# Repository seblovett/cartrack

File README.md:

cartrack
========

A car tracking system using GPS and GSM

Current Capabilities
====================

The GSM has been prototyped and proven to work. 

PCB is V1.0 and not been made nor tested.

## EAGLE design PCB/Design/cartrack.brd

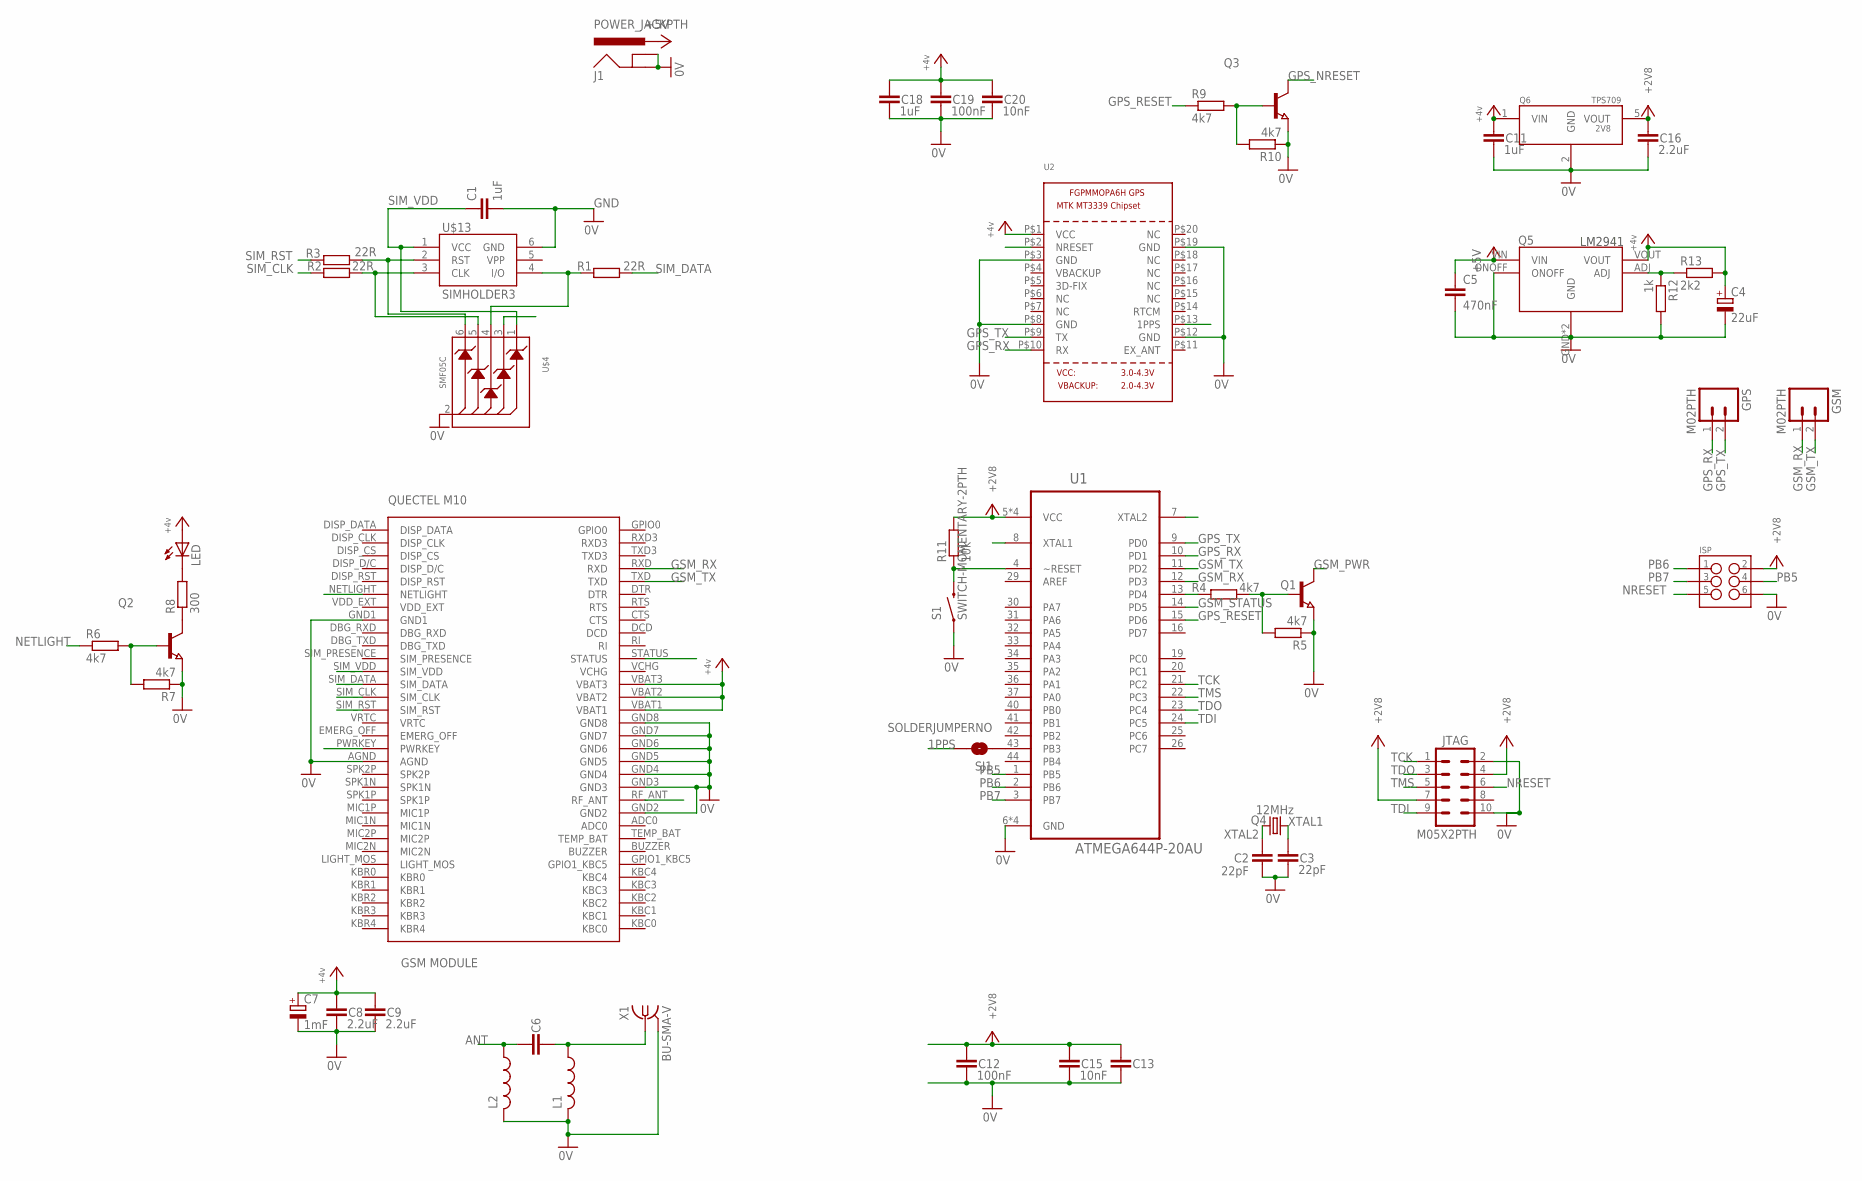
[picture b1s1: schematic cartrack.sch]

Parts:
C1: 1uF; C0603
C2, C3: 22pF; 0603-CAP
C4: 22uF; E3,5-8
C5: 470nF; C025-024X044
C6, C13: CAP0603-CAP; 0603-CAP
C7: 1mF; E3,5-8
C8, C9, C16: 2.2uF; 1206
C11: 1uF; 1206
C12, C19: 100nF; 1206
C15, C20: 10nF; 0603-CAP
C18: 1uF; CAP-PTH-SMALL
GPS: M02PTH; 1X02
GSM: M02PTH; 1X02
ISP: M03X2NO_SILK; 2X3-NS
J1: POWER_JACKPTH; POWER_JACK_PTH
JTAG: M05X2PTH; AVR_ICSP
L1, L2: L-USL2012C; L2012C
LED: LEDSML0603; SML0603
Q1, Q2, Q3: NPN-TRANSISTOR_SOT23W; SOT23W
Q4: 12MHz; SM49
Q5: LM2941
Q6: TPS70928; SOT23-5
R1, R2, R3: 22R; R0603
R4, R5, R6, R7, R9, R10: 4k7; R0603
R8: 300; R0603
R11: 10k; R0603
R12: 1k; R0603
R13: 2k2; R0603
S1: SWITCH-MOMENTARY-2PTH; TACTILE-PTH
SJ1: SOLDERJUMPERNO; SJ_2S-NO
U1: ATMEGA644P-20AU; QFP80P1200X1200X120-44N
U2: GPS_FGPMMOPA6H; FGPMMOPA6H
U$1: QUECTELM10
U$4: SMF05C; SC-88
U$13: SIMHOLDER3
X1: BU-SMA-V

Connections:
1PPS: SJ1.2, U2.P$13 (1PPS)
+2V8: C12.1, C13.1, C15.1, C16.1, ISP.2, JTAG.4, JTAG.7, Q6.5 (VOUT), R11.2, U1.5 (VCC), U1.17 (VCC), U1.27 (VCC), U1.38 (VCC)
+4V: C4.+, C7.+, C8.1, C9.1, C11.1, C18.1, C19.1, C20.1, LED.A, Q5.VOUT, Q6.1 (VIN), R13.2, U2.P$1 (VCC), U$1.VBAT1, U$1.VBAT2, U$1.VBAT3
+5V: C5.1, J1.PWR, Q5.VIN
ANT: C6.1, L2.1, U$1.RF_ANT
ANT_1: C6.2, L1.1, X1.1
GND: C1.2, C2.2, C3.2, C4.-, C5.2, C7.-, C8.2, C9.2, C11.2, C12.2, C13.2, C15.2, C16.2, C18.2, C19.2, C20.2, ISP.6, J1.GND, J1.GNDBREAK, JTAG.2, JTAG.10, L1.2, L2.2, Q1.3 (E), Q2.3 (E), Q3.3 (E), Q5.GND, Q5.ONOFF, Q5.TAB (GND), Q6.2 (GND), R5.1, R7.1, R10.1, R12.2, S1.1, U2.P$3 (GND), U2.P$8 (GND), U2.P$12 (GND), U2.P$19 (GND), U$1.AGND, U$1.GND1, U$1.GND2, U$1.GND3, U$1.GND4, U$1.GND5, U$1.GND6, U$1.GND7, U$1.GND8, U$4.2 (ANODE), U$13.6 (GND), X1.2, X1.3 (2), X1.4 (2), X1.5 (2)
GPS_NRESET: Q3.2 (C), U2.P$2 (NRESET)
GPS_RESET: R9.1, U1.15 (PD6)
GPS_RX: GPS.1, U1.10 (PD1), U2.P$10 (RX)
GPS_TX: GPS.2, U1.9 (PD0), U2.P$9 (TX)
GSM_PWR: Q1.2 (C), U$1.PWRKEY, U$4.3 (CATODE2)
GSM_RX: GSM.1, U1.12 (PD3), U$1.RXD
GSM_STATUS: U1.14 (PD5), U$1.STATUS
GSM_TX: GSM.2, U1.11 (PD2), U$1.TXD
unnamed: Q1.1 (B), R4.2, R5.2
unnamed: R4.1, U1.13 (PD4)
unnamed: Q5.ADJ, R12.1, R13.1
unnamed: Q2.1 (B), R6.2, R7.2
unnamed: Q2.2 (C), R8.1
unnamed: LED.C, R8.2
unnamed: Q3.1 (B), R9.2, R10.2
unnamed: SJ1.1, U1.43 (PB3)
NETLIGHT: R6.1, U$1.NETLIGHT
NRESET: ISP.5, JTAG.6, R11.1, S1.3 (2), U1.4 (~RESET)
PB5: ISP.4, U1.1 (PB5)
PB6: ISP.1, U1.2 (PB6)
PB7: ISP.3, U1.3 (PB7)
SIM_CLK: R2.1, U$1.SIM_CLK
SIM_CLK_R: R2.2, U$4.5 (CATODE4), U$13.3 (CLK)
SIM_DATA: R1.2, U$1.SIM_DATA
SIM_DATA_R: R1.1, U$4.4 (CATODE3), U$13.4 (I/O)
SIM_RST: R3.1, U$1.SIM_RST
SIM_RST_R: R3.2, U$4.6 (CATODE5), U$13.2 (RST)
SIM_VDD: C1.1, U$1.SIM_VDD, U$4.1 (CATODE1), U$13.1 (VCC)
TCK: JTAG.1, U1.21 (PC2)
TDI: JTAG.9, U1.24 (PC5)
TDO: JTAG.3, U1.23 (PC4)
TMS: JTAG.5, U1.22 (PC3)
XTAL1: C3.1, Q4.2, U1.8 (XTAL1)
XTAL2: C2.1, Q4.1, U1.7 (XTAL2)

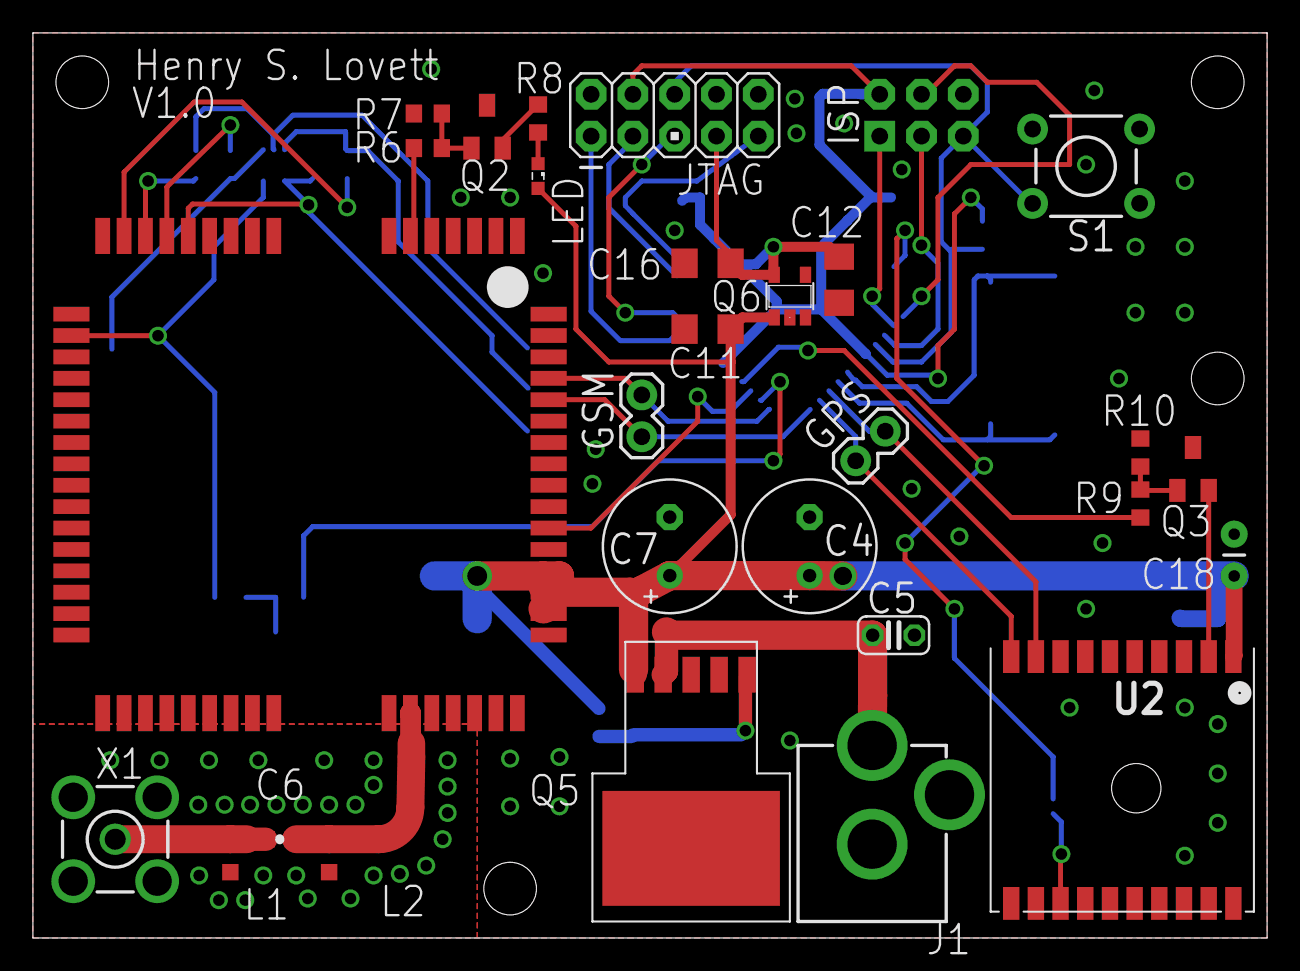
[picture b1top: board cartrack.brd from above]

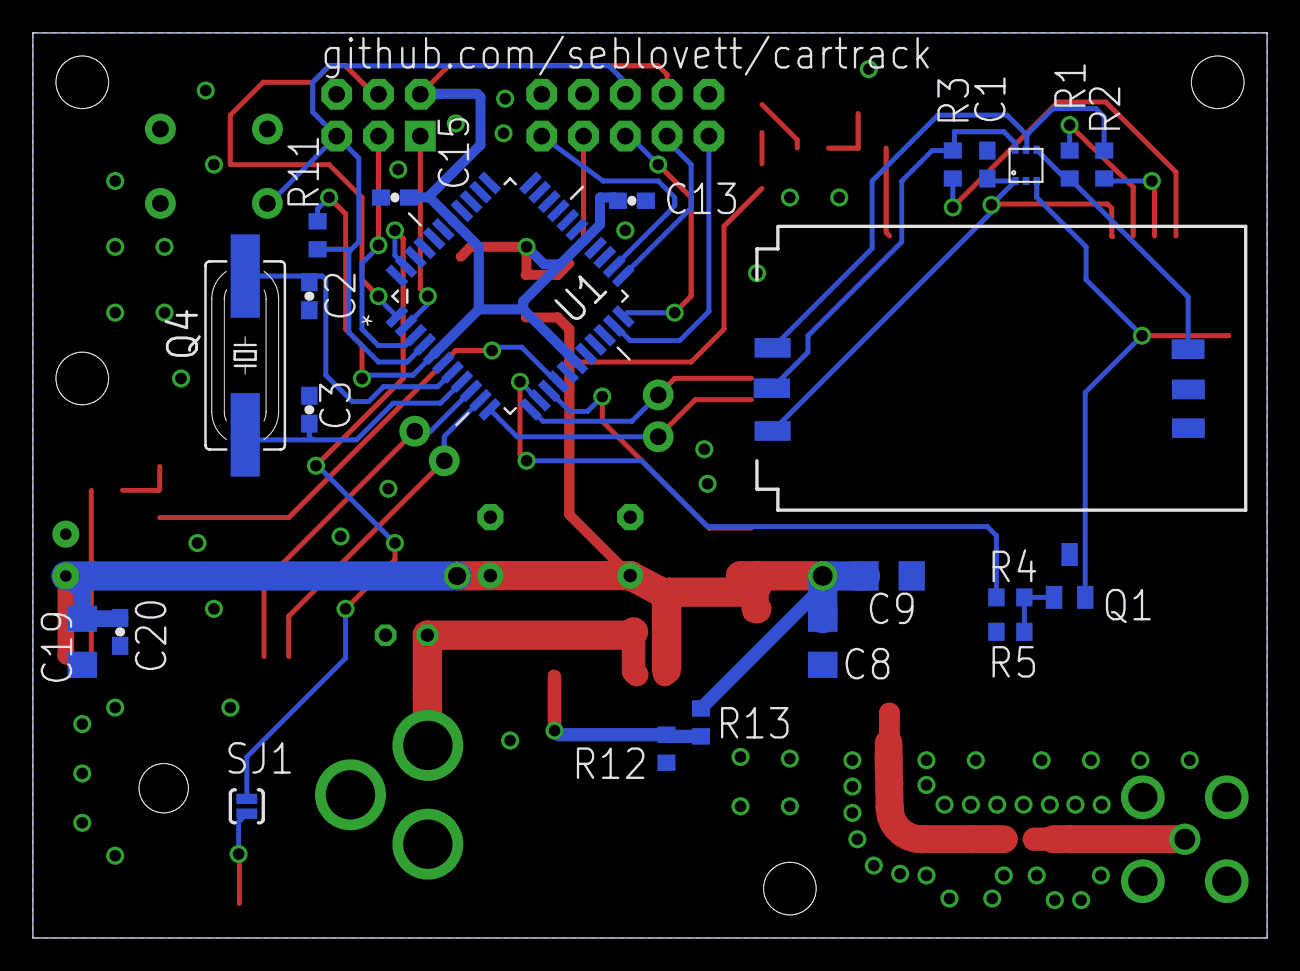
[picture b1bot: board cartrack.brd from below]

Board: 2 copper layers, 75.0 x 55.0 mm, 52 parts (23 on the bottom side), 41 nets.

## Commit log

2014-04-18 First draft of the spec
2014-04-18 Added listings and changed date format
2014-04-19 Started the PCB schematic and design.
2014-04-19 Added library files for gps and gsm
2014-04-19 Added eagle temp files to the ignore
2014-04-19 Added ideas about reporting the credit on the sim card
2014-06-15 Got basic printf working.
2014-06-15 Added Debug compile folder to ignore
2014-06-15 Got a circular buffer working
2014-06-15 Got AT OK working.
    Timeout implemented. Will power on the GSM also
2014-06-15 Got GPRS Submission working well
2014-06-16 Corrected set up
2014-06-16 Removed unnecessary defines
2014-06-16 Neatened up the code.
    Doxygened the hell out of it
2014-06-16 Corrected a debug string. Everything still works
2014-06-16 Done most of the GSM schematic.
    Power and GPS remain
2014-06-16 Added GPS to schematic. Need to do power
2014-06-16 Added all major components to schematic.
    Need to do the antenna, decoupling capacitors and layout
2014-06-16 Added temp library files to gitignore
2014-06-16 added to do list to schematic
2014-06-16 Added Bill of Materials
2014-06-17 Finished schematic.
    Started on PCB.
2014-06-17 Corrected some errors in the library.
    Keepout in the M10 - stops ground planes. Removed the via layer too
    Polygon width to satisy the DRC
2014-06-17 First draft of the PCB
2014-06-18 Redone the PCB layout. Corrected mask and pad errors in the libraries
2014-06-18 Some changes to the antenna
2014-07-22 I can't remember what I have done... but it was probably important.

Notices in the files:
parts and their libraries:
SparkFun-Connectors: Licensing: Creative Commons ShareAlike 4.0 International - https://creativecommons.org/licenses/by-sa/4.0
